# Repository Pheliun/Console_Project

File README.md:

This was my final project to get my Cyber Diploma.
It involved creating a basic functional console that when connected to a power supply (using micro usb b), will be able to utilize a microprocessor, with a display, micro sd card socket, and buttons.
For a detailed explanation regarding my project, here is my project book: https://docs.google.com/document/d/1XIzdJ6GN7S2lS_oo8KrGg07EBY5Gj0uBNZ1zpXOEC-Y/edit?tab=t.0#heading=h.eh6wjaswymlv

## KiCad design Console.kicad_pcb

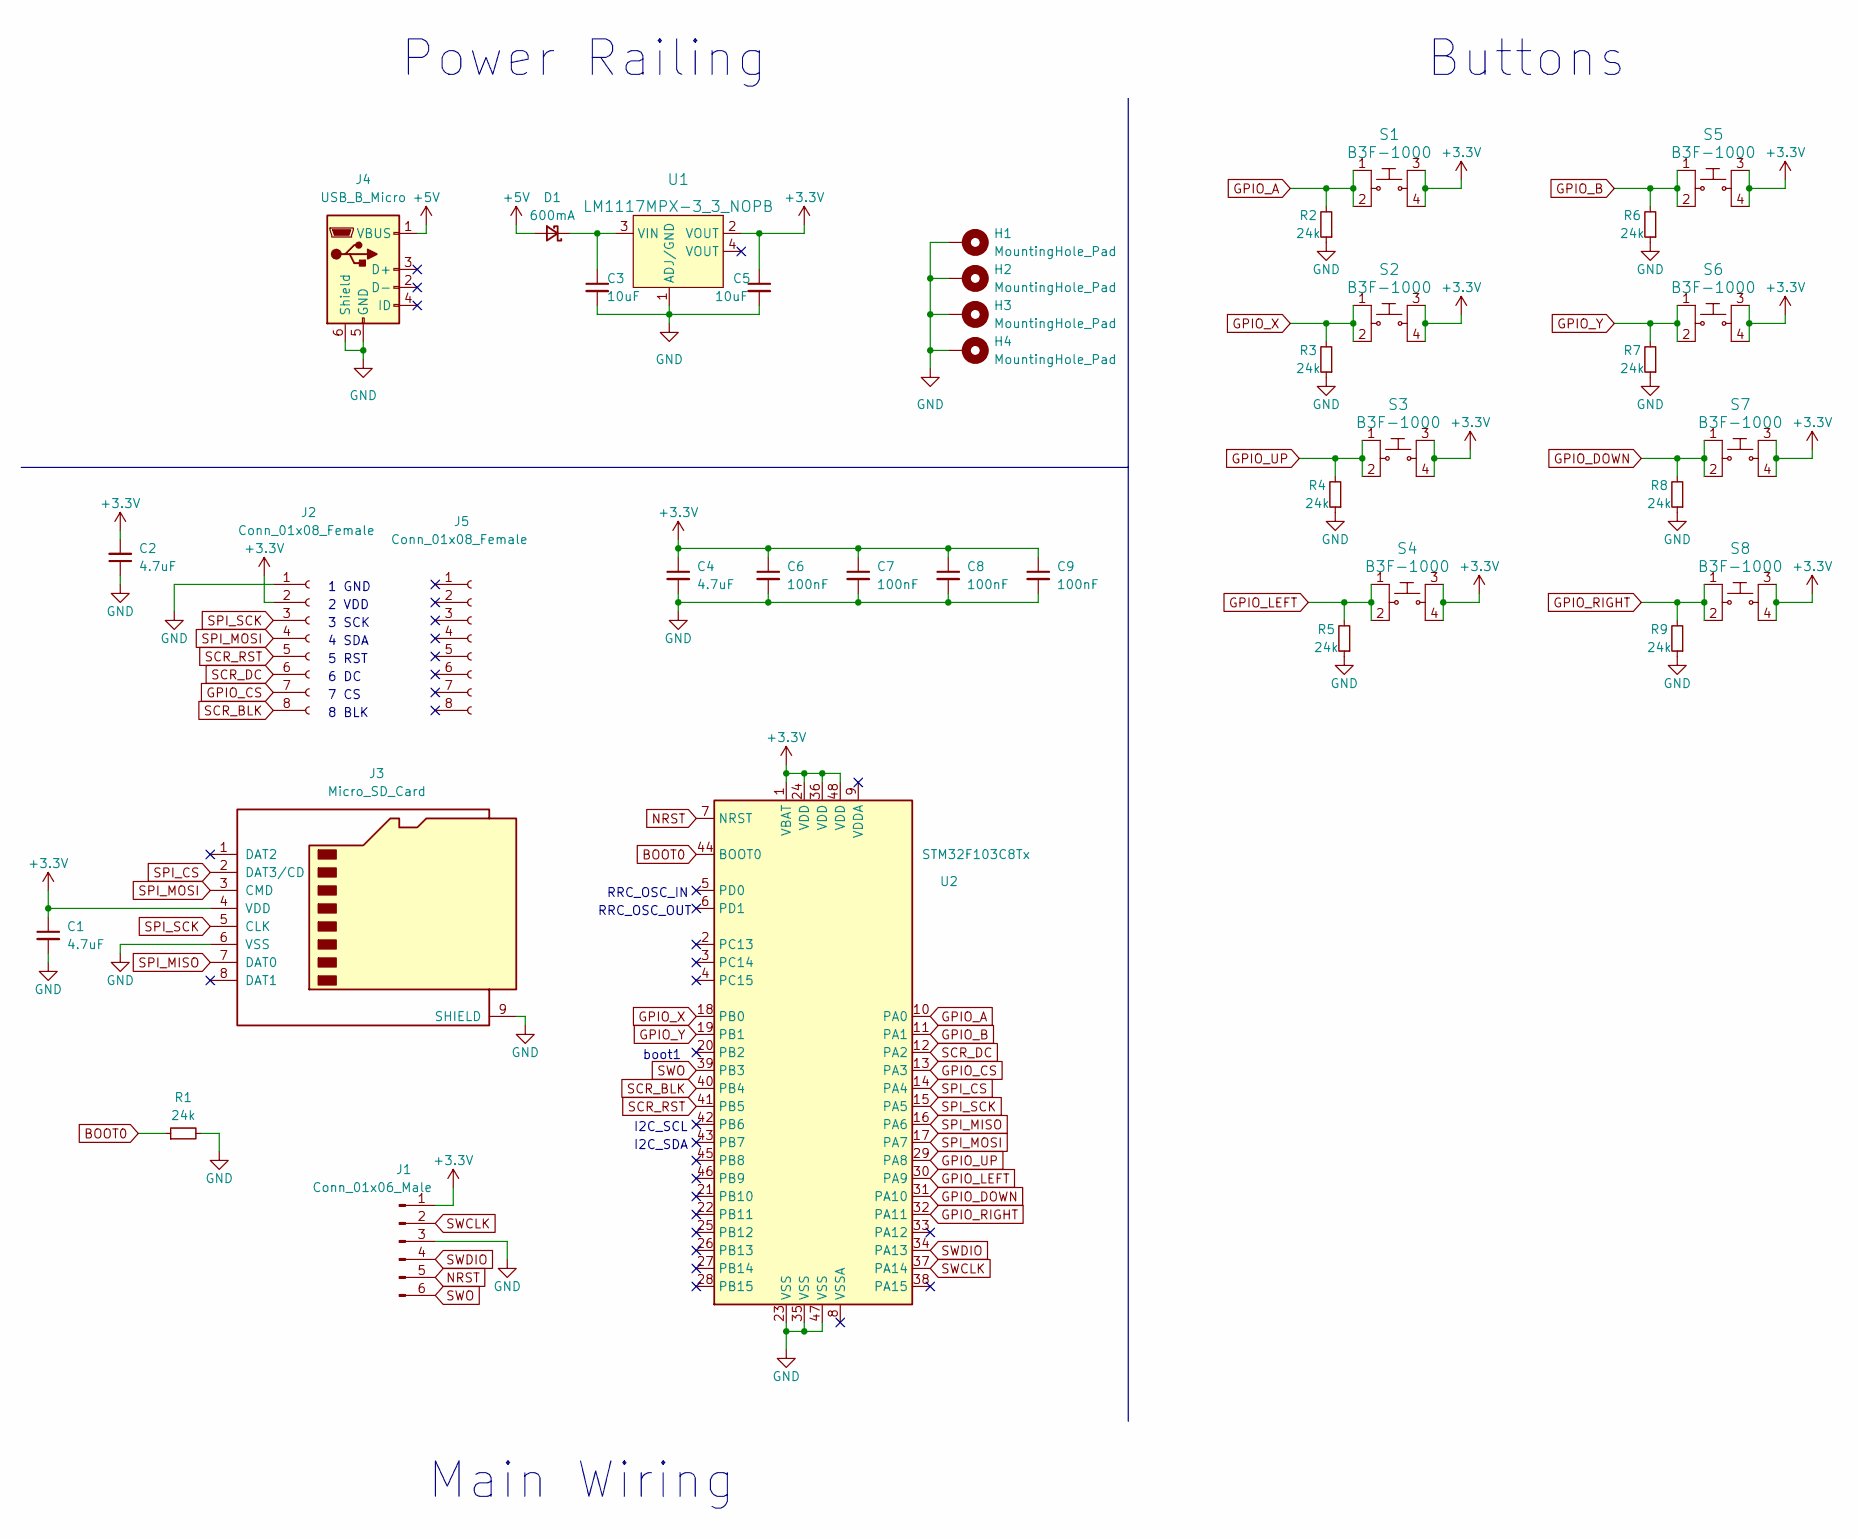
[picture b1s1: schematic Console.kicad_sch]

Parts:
C1, C2, C4: 4.7uF; C_0805_2012Metric; LCSC Part # C1779
C3, C5: 10uF; C_1206_3216Metric; LCSC Part # C13585
C6, C7, C8, C9: 100nF; C_0402_1005Metric; LCSC Part # C24497
D1: 600mA; D_SOD-323; LCSC Part # C191023
H1, H2, H3, H4: MountingHole_Pad; MountingHole_4.3mm_M4_Pad_Via
J1: Conn_01x06_Male; PinHeader_1x06_P2.54mm_Vertical
J2, J5: Conn_01x08_Female; PinSocket_1x08_P2.54mm_Vertical
J3: Micro_SD_Card; microSD_HC_Molex_104031-0811; LCSC Part # C585350
J4: USB_B_Micro; USB_Micro-B_Molex-105133-0001; LCSC Part # C782257
R1, R2, R3, R4, R5, R6, R7, R8, R9: 24k; R_0805_2012Metric; LCSC Part # C17575
S1, S2, S3, S4, S5, S6, S7, S8: B3F-1000; Switch_Tactile_THT_B3F-1xxx; MPN B3F-1000; Digi-Key_PN SW400-ND
U1: LM1117MPX-3_3_NOPB; SOT-223; MPN LM1117MPX-3.3/NOPB; Digi-Key_PN LM1117MPX-3.3/NOPBCT-ND
U2: STM32F103C8Tx; LQFP-48_7x7mm_P0.5mm

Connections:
+3.3V: C1.1, C2.2, C4.1, C5.1, C6.1, C7.1, C8.1, C9.1, J1.1, J2.2, J3.4 (VDD), S1.3, S1.4, S2.3, S2.4, S3.3, S3.4, S4.3, S4.4, S5.3, S5.4, S6.3, S6.4, S7.3, S7.4, S8.3, S8.4, U1.2 (VOUT), U2.1 (VBAT), U2.24 (VDD), U2.36 (VDD), U2.48 (VDD)
+5V: D1.2 (A), J4.1 (VBUS)
BOOT0: R1.1, U2.44 (BOOT0)
GND: C1.2, C2.1, C3.2, C4.2, C5.2, C6.2, C7.2, C8.2, C9.2, H1.1, H2.1, H3.1, H4.1, J1.3, J2.1, J3.6 (VSS), J3.9 (SHIELD), J4.5 (GND), J4.6 (Shield), R1.2, R2.1, R3.1, R4.1, R5.1, R6.1, R7.1, R8.1, R9.1, U1.1 (ADJ/GND), U2.23 (VSS), U2.35 (VSS), U2.47 (VSS)
GPIO_A: R2.2, S1.1, S1.2, U2.10 (PA0)
GPIO_B: R6.2, S5.1, S5.2, U2.11 (PA1)
GPIO_CS: J2.7, U2.13 (PA3)
GPIO_DOWN: R8.2, S7.1, S7.2, U2.31 (PA10)
GPIO_LEFT: R5.2, S4.1, S4.2, U2.30 (PA9)
GPIO_RIGHT: R9.2, S8.1, S8.2, U2.32 (PA11)
GPIO_UP: R4.2, S3.1, S3.2, U2.29 (PA8)
GPIO_X: R3.2, S2.1, S2.2, U2.18 (PB0)
GPIO_Y: R7.2, S6.1, S6.2, U2.19 (PB1)
NRST: J1.5, U2.7 (NRST)
unnamed: C3.1, D1.1 (K), U1.3 (VIN)
SCR_BLK: J2.8, U2.40 (PB4)
SCR_DC: J2.6, U2.12 (PA2)
SCR_RST: J2.5, U2.41 (PB5)
SPI_CS: J3.2 (DAT3/CD), U2.14 (PA4)
SPI_MISO: J3.7 (DAT0), U2.16 (PA6)
SPI_MOSI: J2.4, J3.3 (CMD), U2.17 (PA7)
SPI_SCK: J2.3, J3.5 (CLK), U2.15 (PA5)
SWCLK: J1.2, U2.37 (PA14)
SWDIO: J1.4, U2.34 (PA13)
SWO: J1.6, U2.39 (PB3)

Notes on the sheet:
5 RST
I2C_SCL
boot1
3 SCK
8 BLK
Main Wiring
Power Railing
4 SDA
I2C_SDA
1 GND
2 VDD
7 CS
RRC_OSC_OUT
RRC_OSC_IN
Buttons
6 DC

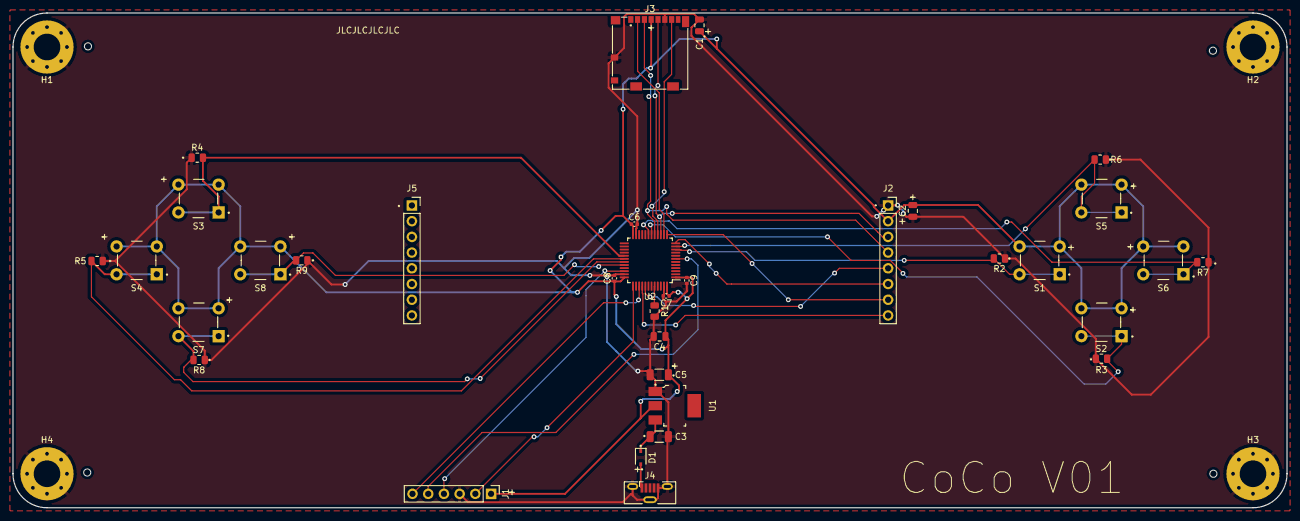
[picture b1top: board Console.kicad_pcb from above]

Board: 2 copper layers, 206.0 x 80.0 mm, 38 parts (0 on the bottom side), 25 nets.

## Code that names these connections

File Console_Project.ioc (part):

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Mcu.Name=STM32F103T(8-B)Ux
Mcu.Package=VFQFPN36
Mcu.UserName=STM32F103TBUx
PA0-WKUP.GPIOParameters=GPIO_Label
PA0-WKUP.GPIO_Label=GPIO_A
PA0-WKUP.Signal=GPXTI0
PA1.GPIOParameters=GPIO_Label
PA1.GPIO_Label=GPIO_B
PA1.Signal=GPXTI1
PA10.GPIOParameters=GPIO_Label
PA10.GPIO_Label=GPIO_DOWN
PA10.Signal=GPXTI10
PA11.GPIOParameters=GPIO_Label
PA11.GPIO_Label=GPIO_RIGHT
PA11.Signal=GPXTI11
PA13.Mode=Trace_Asynchronous_SW
PA13.Signal=SYS_JTMS-SWDIO
PA14.Mode=Trace_Asynchronous_SW
PA14.Signal=SYS_JTCK-SWCLK
PA2.GPIOParameters=GPIO_Label
PA2.GPIO_Label=SCR_DC
PA2.Signal=GPIO_Output
PA3.GPIOParameters=GPIO_Label
PA3.GPIO_Label=SCR_NCS
PA3.Signal=GPIO_Output
PA4.GPIOParameters=GPIO_Label
PA4.GPIO_Label=SD_NCS
PA4.Signal=GPIO_Output
PA5.Mode=Full_Duplex_Master
PA5.Signal=SPI1_SCK
PA6.Mode=Full_Duplex_Master
PA6.Signal=SPI1_MISO
PA7.Mode=Full_Duplex_Master
PA7.Signal=SPI1_MOSI
PA8.GPIOParameters=GPIO_Label
PA8.GPIO_Label=GPIO_UP
PA8.Signal=GPXTI8
PA9.GPIOParameters=GPIO_Label
PA9.GPIO_Label=GPIO_LEFT
PA9.Signal=GPXTI9
PB0.GPIOParameters=GPIO_Label
PB0.GPIO_Label=GPIO_X
PB0.Signal=GPIO_Input
PB1.GPIOParameters=GPIO_Label
PB1.GPIO_Label=GPIO_Y
PB1.Signal=GPIO_Input
PB3.Mode=Trace_Asynchronous_SW
PB3.Signal=SYS_JTDO-TRACESWO
PB4.GPIOParameters=GPIO_Label
PB4.GPIO_Label=SCR_BLK
PB4.Signal=GPIO_Output
PB5.GPIOParameters=GPIO_Label
PB5.GPIO_Label=SCR_RST
PB5.Signal=GPIO_Output
board=custom

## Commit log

2023-03-18 small changes to schematics
2023-03-26 added buttons to schema and changed routes a bit
2023-03-30 sorted the schema
2023-04-15 changed the power railing, switched the boost converter with LDO
2023-04-16 added ILI9341 basic interface
2023-04-16 sorted power rails, assigned footprints etc
2023-04-18 added sd card fatfs library and configured connection, sorted ILI9341 commands into a new file
2023-04-18 added button interrupts and their functions, added CleerScreen to ILI9341_interface
2023-04-18 final commit (hopefully) of V01
2023-04-18 final commit (hopefully) for V01
2023-05-22 fixed problems, switched MCU with another of the same product line
